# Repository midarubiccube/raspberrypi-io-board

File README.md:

# raspberrypi-io-board
## 基板画像

# 概要
- USB PD or 12V DC jack(40Vまで許容)
- 12v-5v, 12v-3.3v, 5v-1.2v DCDCコンバータ搭載
- USB3.0*2
- USB2.0*2
- M.2 M key (NVME SSDのみ) 
- M.2 E key
- gigabit ethernet
- hd*iっぽいなにかの端子
- SDカードスロット
- stm32H723VGT6 搭載
- CANFD*2
- stm32 debug用コネクタ

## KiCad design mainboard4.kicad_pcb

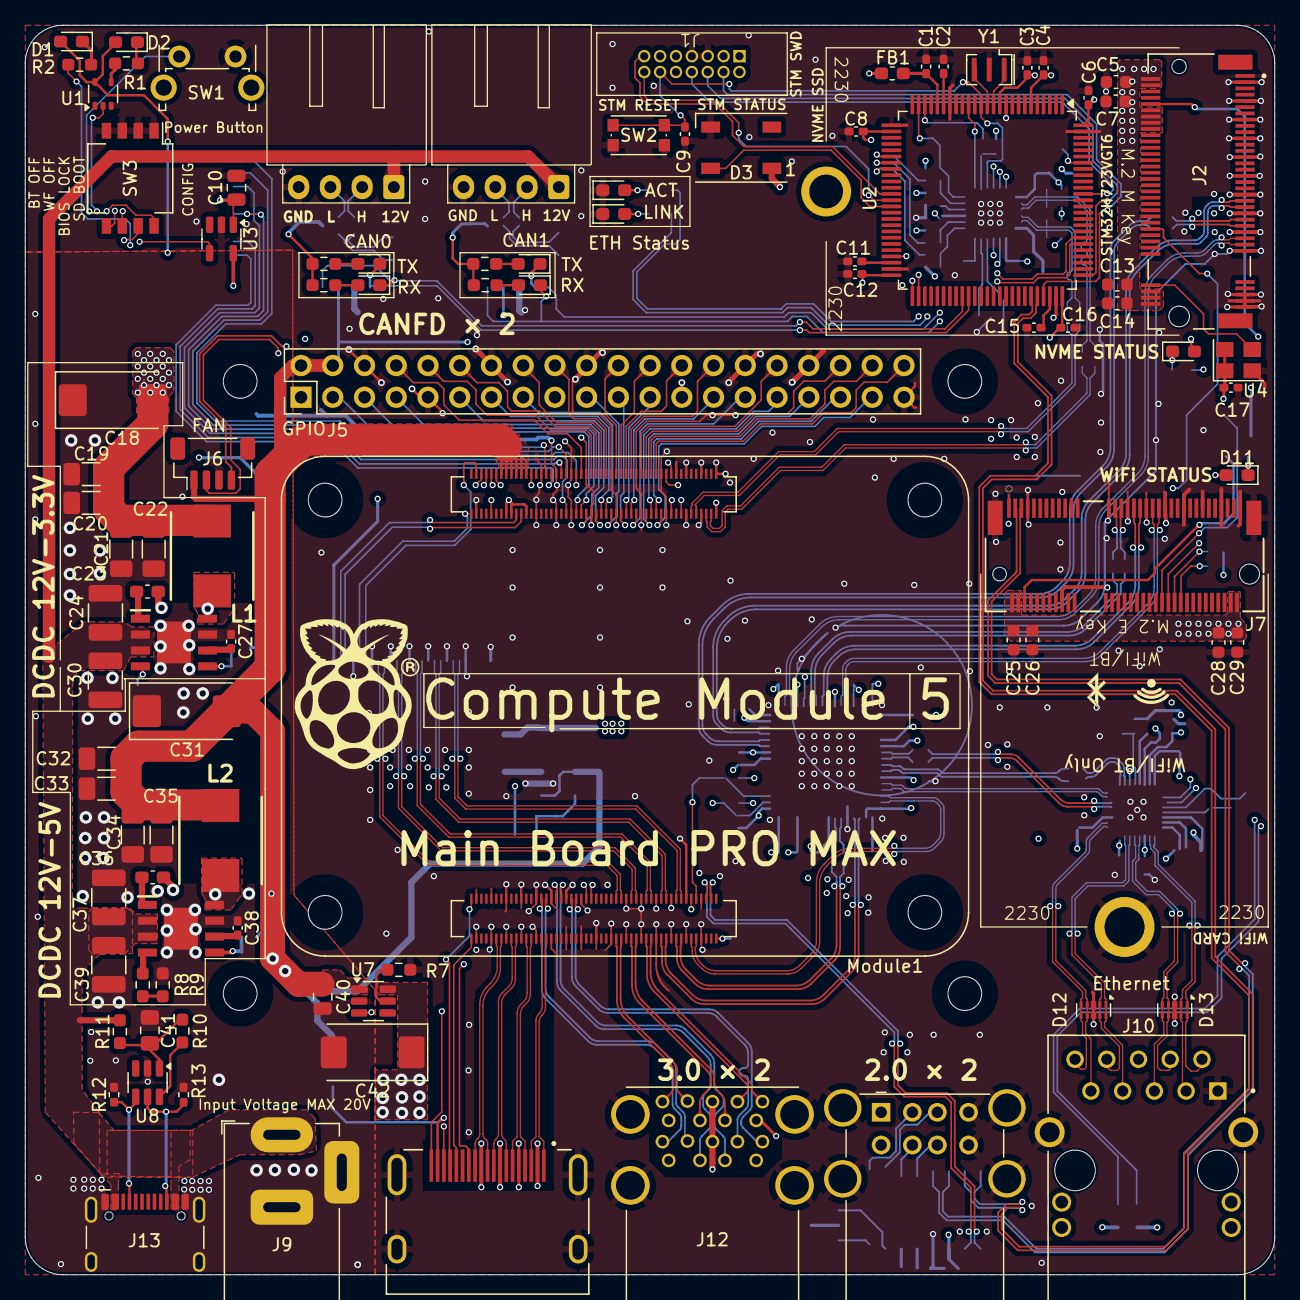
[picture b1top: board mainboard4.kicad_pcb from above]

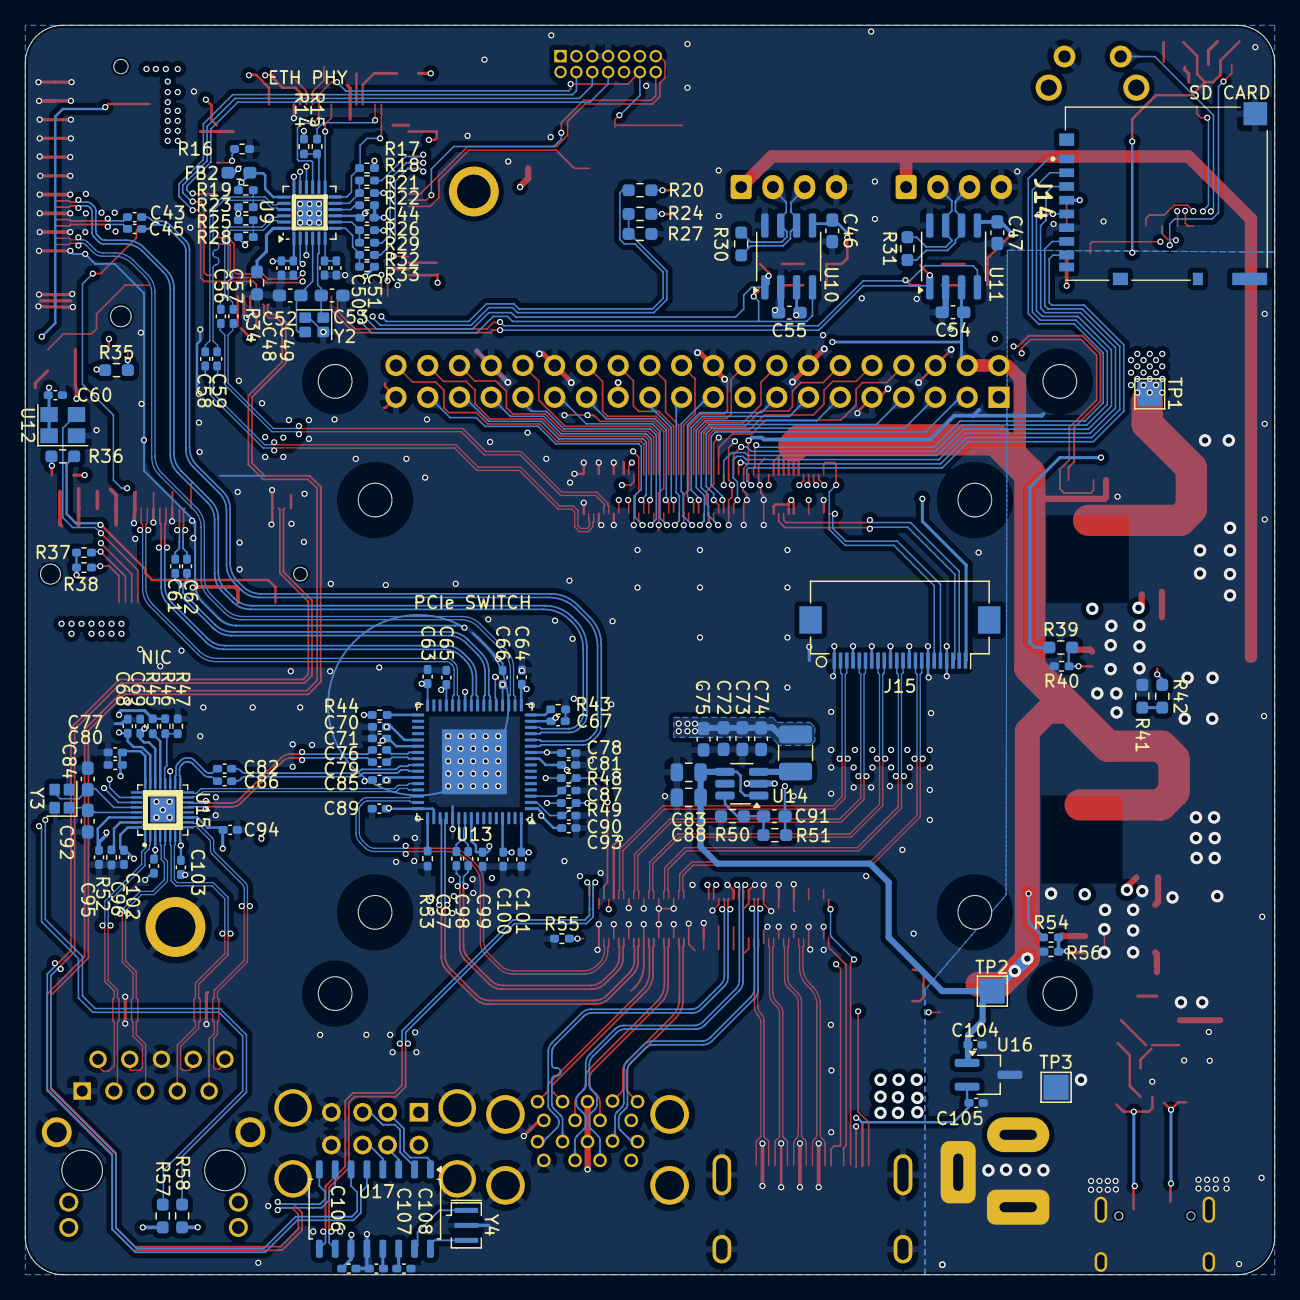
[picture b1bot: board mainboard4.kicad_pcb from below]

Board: 4 copper layers, 100.0 x 100.0 mm, 229 parts (130 on the bottom side), 251 nets.

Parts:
C1, C2, C3, C4, C6, C8, C12, C16, C43, C45, C61, C62, C63, C64, C65, C66, C67, C68, C69, C70, C71, C76, C77, C78, C79, C80, C81, C82, C85, C86, C89, C90, C93, C94, C95, C96, C97, C98, C99, C100, C101, C102, C103: 0.1uF; C_0402_1005Metric_Pad0.74x0.62mm_HandSolder
C5, C7, C13, C25, C26, C29: 0.1uF; C_0603_1608Metric
C9, C11, C15, C44, C48, C49, C56, C57, C58, C59: 0.1μF; C_0402_1005Metric_Pad0.74x0.62mm_HandSolder
C10, C40, C83, C88: 10u; C_0805_2012Metric
C14, C28: 0.01uF; C_0603_1608Metric
C17, C60, C104, C105: 100n; C_0402_1005Metric_Pad0.74x0.62mm_HandSolder
C18, C31: 100uF; CP_EIA-7343-30_AVX-N_Pad2.25x2.55mm_HandSolder
C19, C20, C21, C22, C32, C33, C34, C35: 22uF; C_1206_3216Metric_Pad1.33x1.80mm_HandSolder
C23, C36, C46, C47, C54, C55: 0.1uF; C_0603_1608Metric_Pad1.08x0.95mm_HandSolder
C24, C30, C37, C39: 10μF; C_1210_3225Metric_Pad1.33x2.70mm_HandSolder
C27, C38: 0.01uF; C_0402_1005Metric_Pad0.74x0.62mm_HandSolder
C41: 1μF; C_0805_2012Metric_Pad1.18x1.45mm_HandSolder
C42: 100uF; CP_EIA-7343-31_Kemet-D
C50: 1μF; C_0402_1005Metric_Pad0.74x0.62mm_HandSolder
C51: 470p; C_0402_1005Metric_Pad0.74x0.62mm_HandSolder
C52, C53, C84, C92: 15pF; C_0603_1608Metric_Pad1.08x0.95mm_HandSolder
C72, C73, C74, C75: 10u; C_0603_1608Metric_Pad1.08x0.95mm_HandSolder
C87: 1uF; C_0402_1005Metric_Pad0.74x0.62mm_HandSolder
C91: 22pF; C_0603_1608Metric_Pad1.08x0.95mm_HandSolder
C106, C107, C108: 0.1u; C_0402_1005Metric_Pad0.74x0.62mm_HandSolder
D1, D10, D11: LED Green; LED_0603_1608Metric_Pad1.05x0.95mm_HandSolder
D2: LED Red; LED_0603_1608Metric_Pad1.05x0.95mm_HandSolder
D3: WS2812B; LED_WS2812B_PLCC4_5.0x5.0mm_P3.2mm
D4, D5, D6, D7, D8, D9: LED; LED_0603_1608Metric_Pad1.05x0.95mm_HandSolder
D12, D13: H5VU25U; Diodes_UDFN-10_1.0x2.5mm_P0.5mm
FB1, FB2: FerriteBead; L_0603_1608Metric_Pad1.05x0.95mm_HandSolder
H1, H2: MountingHole; MountingHole_2.7mm_M2.5_DIN965
J1: Conn_02x07_Odd_Even; connector
J2: Bus_M.2_Socket_M; M.2 M Key socket
J3, J4: Conn_01x04_Pin; pocketheader4
J5: THD-20-R; PinHeader_2x20_P2.54mm_Vertical
J6: JST_SHBM04B-SRSS-TB; JST_SH_BM04B-SRSS-TB_1x04-1MP_P1.00mm_Vertical
J7: Bus_M.2_Socket_E; M.2 E Key socket
J8: USB_A_Stacked; USB_A_Wuerth_61400826021_Horizontal_Stacked
J9: Barrel_Jack; BarrelJack_Horizontal
J10: RJMG201K21120FR; AMPHENOL_RJMG201K21120FR
J11: 690-019-298-412; EDAC 690-019-298-412
J12: USB3_A; MTCONN_UBAF30-D2011
J13: USB_C_Receptacle_USB2.0_16P; USB_C_Receptacle_HCTL_HC-TYPE-C-16P-01A
J14: Micro_SD_Card_Det; DM3ATSFPEJM542
J15: Conn_01x22_Female; Hirose_FH12-22S-0.5SH_1x22-1MP_P0.50mm_Horizontal
L1: 6.8; INDPM7066X300N
L2: 6.8uH; INDPM7066X300N
L3: 2.2uH; L_1210_3225Metric_Pad1.42x2.65mm_HandSolder
Module1: Compute Module 5; Raspberry-Pi-5-Compute-Module
R1, R2, R3, R4, R5, R6, R35, R36: 1k; R_0603_1608Metric_Pad0.98x0.95mm_HandSolder
R7: 15K 1%; R_0603_1608Metric_Pad0.98x0.95mm_HandSolder
R8, R9, R41, R42, R50, R51: 100kΩ; R_0603_1608Metric_Pad0.98x0.95mm_HandSolder
R10: 47kΩ; R_0603_1608Metric_Pad0.98x0.95mm_HandSolder
R11: 1kΩ; R_0603_1608Metric_Pad0.98x0.95mm_HandSolder
R12, R13: 5.1kΩ; R_0402_1005Metric_Pad0.72x0.64mm_HandSolder
R14, R21, R26, R33: 10KΩ; R_0402_1005Metric_Pad0.72x0.64mm_HandSolder
R15, R18, R29, R32: 33Ω; R_0402_1005Metric_Pad0.72x0.64mm_HandSolder
R16, R22, R40, R55, R56: 10kΩ; R_0402_1005Metric_Pad0.72x0.64mm_HandSolder
R17: 1.5KΩ; R_0402_1005Metric_Pad0.72x0.64mm_HandSolder
R19, R23, R25, R28: 49.9Ω; R_0402_1005Metric_Pad0.72x0.64mm_HandSolder
R20, R24: 200; R_0603_1608Metric_Pad0.98x0.95mm_HandSolder
R27: 10k; R_0603_1608Metric_Pad0.98x0.95mm_HandSolder
R30, R31: 120Ω; R_0603_1608Metric_Pad0.98x0.95mm_HandSolder
R34: 10kΩ; R_0603_1608Metric_Pad0.98x0.95mm_HandSolder
R37: 1k; R_0402_1005Metric_Pad0.72x0.64mm_HandSolder
R38: 100k; R_0402_1005Metric_Pad0.72x0.64mm_HandSolder
R39: 31.6kΩ; R_0603_1608Metric_Pad0.98x0.95mm_HandSolder
R43, R49, R53: 12.1K; R_0402_1005Metric_Pad0.72x0.64mm_HandSolder
R44, R48: 4.7K; R_0402_1005Metric_Pad0.72x0.64mm_HandSolder
R45, R46, R47: 4.7kΩ; R_0402_1005Metric_Pad0.72x0.64mm_HandSolder
R52: 2.49kΩ; R_0402_1005Metric_Pad0.72x0.64mm_HandSolder
R54: 51.2kΩ; R_0402_1005Metric_Pad0.72x0.64mm_HandSolder
R57, R58: 470R; R_0603_1608Metric_Pad0.98x0.95mm_HandSolder
SW1: Right angle Tact button; SW_Tactile_SPST_Angled_PTS645Vx58-2LFS
SW2: SW_Push; SW_Push_1P1T_NO_CK_KMR2
SW3: SW_DIP_x04; SW_DIP_SPSTx04_Slide_KingTek_DSHP04TS_W7.62mm_P1.27mm
TP1, TP2, TP3: TestPoint; TestPoint_Pad_2.0x2.0mm
U1: 74LVC1G07SE-7; SOT-353_SC-70-5
U2: STM32H723VGT6; LQFP-100_14x14mm_P0.5mm
U3: RT9742GGJ5; SOT-23-5
U4, U12: ASEK-32.768KHZ-L-R-T; Crystal_SMD_3225-4Pin_3.2x2.5mm
U5: AP64502QSP-13; SOIC127P600X163-9N
U6: AP64502; SOIC127P600X163-9N
U7: AP22653W6; SOT-23-6
U8: CH221K; SOT-23-6
U9: LAN8742A; VQFN-24-1EP_4x4mm_P0.5mm_EP2.5x2.5mm
U10, U11: MCP2562-E-SN; SOIC-8_3.9x4.9mm_P1.27mm
U13: QFN-64-1EP_9x9mm_P0.5mm_EP5.2x5.2mm
U14: AP3445LW6-7; SOT-23-6_Handsoldering
U15: RTL8111H-CG-RH; QFN40P400X400X90-33N
U16: RT9742SNGV; TSOT-23_HandSoldering
U17: SL2.1A; SOIC-16_4.55x10.3mm_P1.27mm
Y1: 16Mhz; Resonator_SMD_Murata_CSTxExxV-3Pin_3.0x1.1mm
Y2, Y3: 25Mhz; Crystal_SMD_SeikoEpson_FA128-4Pin_2.0x1.6mm
Y4: 12Mhz; Resonator_SMD_Murata_CSTxExxV-3Pin_3.0x1.1mm

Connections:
+1.2V: C64.2, C65.2, C66.2, C67.2, C70.2, C72.1, C73.1, C74.1, C75.1, C81.2, C85.2, C89.2, C91.1, C100.2, C101.2, L3.2, R51.1, U13.9 (VDD12), U13.15 (VDD12), U13.17 (VCC12), U13.20 (VDD12), U13.26 (VDD12), U13.29 (VCC12), U13.37 (VDD12), U13.43 (VDD12), U13.48 (VCC12), U13.50 (VDD12), U13.61 (VDD12), U13.64 (VCC12)
+3.3V: C3.1, C4.1, C5.1, C6.1, C7.1, C8.1, C12.1, C13.1, C14.1, C16.1, C17.1, C18.2, C19.2, C20.2, C21.2, C22.2, C25.1, C26.1, C28.1, C29.1, C44.1, C46.1, C47.1, C60.1, C63.2, C68.2, C71.2, C78.1, C93.2, C94.2, C96.2, C99.2, D1.2 (A), D2.2 (A), D3.1 (VDD), D10.2 (A), D11.2 (A), FB1.1, FB2.1, J1.3, J2.2 (3.3V), J2.4 (3.3V), J2.12 (3.3V), J2.14 (3.3V), J2.16 (3.3V), J2.18 (3.3V), J2.70 (3.3V), J2.72 (3.3V), J2.74 (3.3V), J7.2 (3.3V), J7.4 (3.3V), J7.72 (3.3V), J7.74 (3.3V), J10.L2, J10.L4, J15.22, L1.2, R3.1, R4.1, R5.1, R6.1, R14.1, R17.1, R21.1, R26.1, R33.1, R37.1, R38.1, R39.1, R44.1, R45.2, R46.2, R48.1, R49.1, TP1.1, U1.5 (VCC), U2.6 (VBAT), U2.11 (VDD), U2.27 (VDD), U2.50 (VDD), U2.75 (VDD), U2.100 (VDD), U3.5 (IN), U4.1 (EN), U4.4 (VDD), U9.9 (VDDIO), U10.5 (Vio), U11.5 (Vio), U12.1 (EN), U12.4 (VDD), U13.1 (VSUS33), U13.10 (VDDA33), U13.21 (VDDA33), U13.32 (VCC3), U13.38 (VDDA33), U13.56 (VDDA33), U15.11 (AVDD33), U15.23 (VDDREG), U15.32 (AVDD33)
+5V: C31.2, C32.2, C33.2, C34.2, C35.2, C40.1, C54.1, C55.1, C83.1, C88.1, C104.1, J5.2, J5.4, J6.1, L2.2, Module1.77 (+5v_(Input)), Module1.79 (+5v_(Input)), Module1.81 (+5v_(Input)), Module1.83 (+5v_(Input)), Module1.85 (+5v_(Input)), Module1.87 (+5v_(Input)), R54.1, TP2.1, U7.1 (IN), U10.3 (VDD), U11.3 (VDD), U14.1 (EN), U14.4 (VIN), U16.1 (IN)
+12V: C24.1, C30.1, C37.1, C39.1, J3.1, J4.1, J9.1, J13.A4 (VBUS), J13.A9 (VBUS), J13.B4 (VBUS), J13.B9 (VBUS), R11.1, U5.2 (VIN), U5.3 (EN), U6.2 (VIN), U6.3 (EN)
/CANFD1/CANN: J3.3, R31.1, U11.6 (CANL)
/CANFD1/CANP: J3.2, R31.2, U11.7 (CANH)
/CANFD1/CANRX: D8.1 (K), U2.59 (PD12), U11.4 (RXD)
/CANFD1/CANTX: D6.1 (K), U2.60 (PD13), U11.1 (TXD)
/CANFD2/CANN: J4.3, R30.1, U10.6 (CANL)
/CANFD2/CANP: J4.2, R30.2, U10.7 (CANH)
/CANFD2/CANRX: D9.1 (K), U2.81 (PD0), U10.4 (RXD)
/CANFD2/CANTX: D7.1 (K), U2.82 (PD1), U10.1 (TXD)
/CM5/3.3V: J5.1, J5.17, Module1.78 (GPIO_VREF(1.8v/3.3v_Input)), Module1.84 (+3.3v_(Output)), Module1.86 (+3.3v_(Output))
/CM5/BT_nDis: Module1.91 (BT_nDisable), SW3.5
/CM5/CEC: J11.13 (CEC), Module1.151 (HDMI0_CEC)
/CM5/CKN: J11.12 (CK-), Module1.190 (HDMI0_CLK_N)
/CM5/CKP: J11.10 (CK+), Module1.188 (HDMI0_CLK_P)
/CM5/D0N: J11.9 (D0-), Module1.184 (HDMI0_TX0_N)
/CM5/D0P: J11.7 (D0+), Module1.182 (HDMI0_TX0_P)
/CM5/D1N: J11.6 (D1-), Module1.178 (HDMI0_TX1_N)
/CM5/D1P: J11.4 (D1+), Module1.176 (HDMI0_TX1_P)
/CM5/D2N: J11.3 (D2-), Module1.172 (HDMI0_TX2_N)
/CM5/D2P: J11.1 (D2+), Module1.170 (HDMI0_TX2_P)
/CM5/DSI0N: J15.2, Module1.115 (MIPI0_D0_N)
/CM5/DSI0P: J15.3, Module1.117 (MIPI0_D0_P)
/CM5/DSI1N: J15.5, Module1.121 (MIPI0_D1_N)
/CM5/DSI1P: J15.6, Module1.123 (MIPI0_D1_P)
/CM5/DSI2N: J15.11, Module1.133 (MIPI0_D2_N)
/CM5/DSI2P: J15.12, Module1.135 (MIPI0_D2_P)
/CM5/DSI3N: J15.14, Module1.139 (MIPI0_D3_N)
/CM5/DSI3P: J15.15, Module1.141 (MIPI0_D3_P)
/CM5/DSICN: J15.8, Module1.127 (MIPI0_C_N)
/CM5/DSICP: J15.9, Module1.129 (MIPI0_C_P)
/CM5/EEPROM_nWP: Module1.20 (EEPROM_nWP), SW3.7
/CM5/GPIO0: J15.17, Module1.97 (CAM_GPIO0)
/CM5/GPIO1: J15.18, Module1.100 (CAM_GPIO1)
/CM5/GPIO2: J5.3, Module1.58 (GPIO2)
/CM5/GPIO3: J5.5, Module1.56 (GPIO3)
/CM5/GPIO4: J5.7, Module1.54 (GPIO4)
/CM5/GPIO5: J5.29, Module1.34 (GPIO5)
/CM5/GPIO6: J5.31, Module1.30 (GPIO6)
/CM5/GPIO7: J5.26, Module1.37 (GPIO7)
/CM5/GPIO8: J5.24, Module1.39 (GPIO8)
/CM5/GPIO9: J5.21, Module1.40 (GPIO9)
/CM5/GPIO10: J5.19, Module1.44 (GPIO10)
/CM5/GPIO11: J5.23, Module1.38 (GPIO11)
/CM5/GPIO12: J5.32, Module1.31 (GPIO12)
/CM5/GPIO13: J5.33, Module1.28 (GPIO13)
/CM5/GPIO14: J5.8, Module1.55 (GPIO14)
/CM5/GPIO15: J5.10, Module1.51 (GPIO15)
/CM5/GPIO16: J5.36, Module1.29 (GPIO16)
/CM5/GPIO17: J5.11, Module1.50 (GPIO17)
/CM5/GPIO18: J5.12, Module1.49 (GPIO18)
/CM5/GPIO19: J5.35, Module1.26 (GPIO19)
/CM5/GPIO20: J5.38, Module1.27 (GPIO20)
/CM5/GPIO21: J5.40, Module1.25 (GPIO21)
/CM5/GPIO22: J5.15, Module1.46 (GPIO22)
/CM5/GPIO23: J5.16, Module1.47 (GPIO23)
/CM5/GPIO24: J5.18, Module1.45 (GPIO24)
/CM5/GPIO25: J5.22, Module1.41 (GPIO25)
/CM5/GPIO26: J5.37, Module1.24 (GPIO26)
/CM5/GPIO27: J5.13, Module1.48 (GPIO27)
/CM5/HOST.CLKN: Module1.112 (PCIe_CLK_N), U13.46 (REFCLKP_0)
/CM5/HOST.CLKP: Module1.110 (PCIe_CLK_P), U13.47 (REFCLKN_0)
/CM5/HOST.CLKREQ: Module1.102 (PCIe_nCLKREQ), R55.2
/CM5/HOST.RXN: C97.1, Module1.118 (PCIe_RX_N)
/CM5/HOST.RXP: C98.1, Module1.116 (PCIe_RX_P)
/CM5/HOST.TXN: Module1.124 (PCIe_TX_N), U13.51 (RXP_0)
/CM5/HOST.TXP: Module1.122 (PCIe_TX_P), U13.52 (RXN_0)
/CM5/HPD: J11.19 (HPD/HEAC-), Module1.153 (HDMI0_HOTPLUG)
/CM5/ID_SC: J5.28, Module1.35 (ID_SC)
/CM5/ID_SD: J5.27, Module1.36 (ID_SD)
/CM5/LED_nACT: Module1.21 (LED_nACT), R2.2
/CM5/PCIe_nRST: C87.2, Module1.109 (PCIe_nRST), R48.2, U13.3 (PE_RST)
/CM5/POWER_SW: Module1.92 (PWR_BUT), SW1.1
/CM5/PWM: J6.2, Module1.19 (FAN_PWM)
/CM5/PWR_ON: Module1.75 (SD_PWR_ON), U3.4 (EN)
/CM5/SCL: J11.15 (SCL), Module1.200 (HDMI0_SCL)
/CM5/SDA: J11.16 (SDA), Module1.199 (HDMI0_SDA)
/CM5/SD_CLK: J14.5 (CLK), Module1.57 (SD_CLK)
/CM5/SD_CMD: J14.3 (CMD), Module1.62 (SD_CMD)
/CM5/SD_DAT0: J14.7 (DAT0), Module1.63 (SD_DAT0)
/CM5/SD_DAT1: J14.8 (DAT1), Module1.67 (SD_DAT1)
/CM5/SD_DAT2: J14.1 (DAT2), Module1.69 (SD_DAT2)
/CM5/SD_DAT3: J14.2 (DAT3/CD), Module1.61 (SD_DAT3)
/CM5/TACHO: J6.4, Module1.16 (FAN_TACHO)
/CM5/TP_SCL: J15.20, Module1.80 (SCL0)
/CM5/TP_SDA: J15.21, Module1.82 (SDA0)
/CM5/TRD0_N: C56.1, Module1.10 (Ethernet_Pair0_N)
/CM5/TRD0_P: C57.1, Module1.12 (Ethernet_Pair0_P)
/CM5/TRD1_N: C58.1, Module1.6 (Ethernet_Pair1_N)
/CM5/TRD1_P: C59.1, Module1.4 (Ethernet_Pair1_P)
/CM5/USB0.DN: J12.B2 (D-), Module1.136 (USB3-0-D_N)
/CM5/USB0.DP: J12.B3 (D+), Module1.134 (USB3-0-D_P)
/CM5/USB0.RXN: J12.B5 (SSRX-), Module1.128 (USB3-0-RX_N)
/CM5/USB0.RXP: J12.B6 (SSRX+), Module1.130 (USB3-0-RX_P)
/CM5/USB0.TXN: J12.B8 (SSTX-), Module1.140 (USB3-0-TX_N)
/CM5/USB0.TXP: J12.B9 (SSTX+), Module1.142 (USB3-0-TX_P)
/CM5/USB1.DN: J12.A2 (D-), Module1.165 (USB3-1-D_N)
/CM5/USB1.DP: J12.A3 (D+), Module1.163 (USB3-1-D_P)
/CM5/USB1.RXN: J12.A5 (SSRX-), Module1.157 (USB3-1-RX_N)
/CM5/USB1.RXP: J12.A6 (SSRX+), Module1.159 (USB3-1-RX_P)
/CM5/USB1.TXN: J12.A8 (SSTX-), Module1.169 (USB3-1-TX_N)
/CM5/USB1.TXP: J12.A9 (SSTX+), Module1.171 (USB3-1-TX_P)
/CM5/USB2.DN: Module1.103 (USB2_N), U17.9 (UDM)
/CM5/USB2.DP: Module1.105 (USB2_P), U17.10 (UDP)
/CM5/VBUS_EN: Module1.111 (VBUS_EN), U7.3 (EN)
/CM5/WL_nDis: Module1.89 (WiFi_nDisable), SW3.6
/CM5/nPWR_LED: Module1.95 (LED_nPWR), U1.2
/CM5/nRPIBOOT: Module1.93 (nRPIBOOT), SW3.8
/CM5_INTERFACE/GPDI_5v: C105.1, J11.18 (+5V), U16.2 (OUT)
/Ethernet PHY/CRSDV: R18.2, U2.31 (PA7)
/Ethernet PHY/MDC: U2.16 (PC1), U9.13 (MDC)
/Ethernet PHY/MDIO: R17.2, U2.24 (PA2), U9.12 (MDIO)
/Ethernet PHY/REFCLK: R15.1, U2.23 (PA1)
/Ethernet PHY/RXC_N: C56.2, R25.2, U9.22 (RXN)
/Ethernet PHY/RXC_P: C57.2, R28.2, U9.23 (RXP)
/Ethernet PHY/RXD0: R29.2, U2.32 (PC4)
/Ethernet PHY/RXD1: R32.2, U2.33 (PC5)
/Ethernet PHY/TXC_N: C58.2, R19.2, U9.20 (TXN)
/Ethernet PHY/TXC_P: C59.2, R23.2, U9.21 (TXP)
/Ethernet PHY/TXD0: U2.51 (PB12), U9.17 (TXD0)
/Ethernet PHY/TXD1: U2.52 (PB13), U9.18 (TXD1)
/Ethernet PHY/TXEN: U2.47 (PB11), U9.16 (TXEN)
/MCU/LED: D3.4 (DIN), U2.39 (PE9)
/MCU/MCU.DN: U2.70 (PA11), U17.7 (DM1)
/MCU/MCU.DP: U2.71 (PA12), U17.8 (DP1)
/MCU/SWCLK: J1.6, U2.76 (PA14(JTCK)
/MCU/SWDIO: J1.4, U2.72 (PA13(JTMS)
/MCU/SWO: J1.8, U2.89 (PB3(JTDO)
/MCU/UART_RX: J1.13, U2.37 (PE7)
/MCU/UART_TX: J1.14, U2.38 (PE8)
/MCU/VDDA: C1.1, FB1.2, U2.21 (VDDA)
/MCU/~RST: C9.1, J1.12, SW2.2, U2.14 (NRST), U9.15 (~RST)
/NIC/1.0V: C69.2, C77.2, C80.2, C95.2, C102.2, C103.2, U15.3 (AVDD10), U15.8 (AVDD10), U15.22 (DVDD10), U15.24 (REGOUT), U15.30 (AVDD10)
/NIC/ETH_LEDG: R57.2, U15.27 (LED0)
/NIC/ETH_LEDY: R58.2, U15.26 (LED1)
/NIC/HSON: C86.2, U15.17 (HSOP)
/NIC/HSOP: C82.2, U15.18 (HSON)
/NIC/MDI0+: D13.1, D13.10 (NC), J10.P2 (TD1+), U15.1 (MDIP0)
/NIC/MDI0-: D13.2, D13.9 (NC), J10.P3 (TD1-), U15.2 (MDIN0)
/NIC/MDI1+: D13.4, D13.7 (NC), J10.P4 (TD2+), U15.4 (MDIP1)
/NIC/MDI1-: D13.5, D13.6 (NC), J10.P5 (TD2-), U15.5 (MDIN1)
/NIC/MDI2+: D12.1, D12.10 (NC), J10.P7 (TD3+), U15.6 (MDIP2)
/NIC/MDI2-: D12.2, D12.9 (NC), J10.P8 (TD3-), U15.7 (MDIN2)
/NIC/MDI3+: D12.4, D12.7 (NC), J10.P9 (TD4+), U15.9 (MDIP3)
/NIC/MDI3-: D12.5, D12.6 (NC), J10.P10 (TD4-), U15.10 (MDIN3)
/NIC/NIC.CLKN: U13.45 (REFCLKN_7), U15.15 (REFCLK_P)
/NIC/NIC.CLKP: U13.44 (REFCLKP_7), U15.16 (REFCLK_N)
/NIC/NIC.RXN: C86.1, U13.42 (RXN_7)
/NIC/NIC.RXP: C82.1, U13.41 (RXP_7)
/NIC/NIC.TXN: C79.1, U15.13 (HSIP)
/NIC/NIC.TXP: C76.1, U15.14 (HSIN)
/NIC/nRST: C90.2, J2.50 (~PERST), J7.52 (~PERST0), R49.2, U13.2 (PE_RST_OUT), U15.19 (PERSTB)
/NVME/NVME.CLKN: J2.55 (REFCLKp), U13.19 (REFCLKN_3)
/NVME/NVME.CLKP: J2.53 (REFCLKn), U13.18 (REFCLKP_3)
/NVME/NVME.RXN: J2.43 (PERp0/SATA-B-), U13.14 (RXN_3)
/NVME/NVME.RXP: J2.41 (PERn0/SATA-B+), U13.13 (RXP_3)
/NVME/NVME.TXN: C43.1, J2.47 (PETn0/SATA-A-)
/NVME/NVME.TXP: C45.1, J2.49 (PETp0/SATA-A+)
/PCIe_SW/HOST.RXCN: C98.2, U13.55 (TXN_0)
/PCIe_SW/HOST.RXCP: C97.2, U13.54 (TXP_0)
/PCIe_SW/NIC.TXCN: C79.2, U13.40 (TXN_7)
/PCIe_SW/NIC.TXCP: C76.2, U13.39 (TXP_3)
/PCIe_SW/NVME.TXCN: C45.2, U13.12 (TXN_3)
/PCIe_SW/NVME.TXCP: C43.2, U13.11 (TXP_3)
/PCIe_SW/WiFi.CLKN: J7.49 (REFCLKn0), U13.28 (REFCLKN_5)
/PCIe_SW/WiFi.CLKP: J7.47 (REFCLKp0), U13.27 (REFCLKP_5)
/PCIe_SW/WiFi.RXN: J7.43 (PERn0), U13.25 (RXN_5)
/PCIe_SW/WiFi.RXP: J7.41 (PERp0), U13.24 (RXP_5)
/PCIe_SW/WiFi.TXCN: C61.2, U13.23 (TXN_5)
/PCIe_SW/WiFi.TXCP: C62.2, U13.22 (TXP_5)
/PCIe_SW/WiFi.TXN: C61.1, J7.37 (PETn0)
/PCIe_SW/WiFi.TXP: C62.1, J7.35 (PETp0)
/Power/CC1: J13.A5 (CC1), R12.1, U8.4 (CC1)
/Power/CC2: J13.B5 (CC2), R13.1, U8.5 (CC2)
/USB/D3N: J8.6 (D2-), U17.3 (DM3)
/USB/D3P: J8.7 (D2+), U17.4 (DP3)
/USB/D4N: J8.2 (D1-), U17.1 (DM4)
/USB/D4P: J8.3 (D1+), U17.2 (DP4)
/USB/WiFi.DN: J7.5 (USB_D-), U17.5 (DM2)
/USB/WiFi.DP: J7.3 (USB_D+), U17.6 (DP2)
GND: C1.2, C2.2, C3.2, C4.2, C5.2, C6.2, C7.2, C8.2, C9.2, C10.2, C11.2, C12.2, C13.2, C14.2, C15.2, C16.2, C17.2, C18.1, C19.1, C20.1, C21.1, C22.1, C24.2, C25.2, C26.2, C27.1, C28.2, C29.2, C30.2, C31.1, C32.1, C33.1, C34.1, C35.1, C37.2, C38.1, C39.2, C40.2, C41.2, C42.2, C44.2, C46.2, C47.2, C48.2, C49.2, C50.2, C51.2, C52.2, C53.2, C54.2, C55.2, C60.2, C63.1, C64.1, C65.1, C66.1, C67.1, C68.1, C69.1, C70.1, C71.1, C72.2, C73.2, C74.2, C75.2, C77.1, C78.2, C80.1, C81.1, C83.2, C84.2, C85.1, C87.1, C88.2, C89.1, C90.1, C92.2, C93.1, C94.1, C95.1, C96.1, C99.1, C100.1, C101.1, C102.1, C103.1, C104.2, C105.2, C106.2, C107.2, C108.2, D3.3 (VSS), D4.1 (K), D5.1 (K), D12.3 (VSS), D12.8 (VSS), D13.3 (VSS), D13.8 (VSS), J1.5, J1.7, J2.1 (GND), J2.3 (GND), J2.9 (GND), J2.15 (GND), J2.21 (GND), J2.27 (GND), J2.33 (GND), J2.39 (GND), J2.45 (GND), J2.51 (GND), J2.57 (GND), J2.71 (GND), J2.73 (GND), J2.75 (GND), J3.4, J4.4, J5.6, J5.9, J5.14, J5.20, J5.25, J5.30, J5.34, J5.39, J6.3, J7.1 (GND), J7.7 (GND), J7.18 (GND), J7.33 (GND), J7.39 (GND), J7.45 (GND), J7.51 (GND), J7.57 (GND), J7.63 (GND), J7.69 (GND), J7.75 (GND), J7.76 (GND), J7.77 (GND), J7.M1 (GND), J8.4 (GND1), J8.8 (GND2), J8.9 (Shield), J9.2, J9.3, J10.P1 (GND), J10.P6 (TCT), J10.S1 (SHIELD), J10.S2 (SHIELD__1), J11.2 (D2S), J11.5 (D1S), J11.8 (D0S), J11.11 (CKS), J11.17 (GND), J11.SH1 (SH), J11.SH2 (SH), J11.SH3 (SH), J11.SH4 (SH), J12.10 (SHIELD), J12.A4 (GND), J12.A7 (DRAIN), J12.B4 (GND), J12.B7 (DRAIN), J13.A1 (GND), J13.A12 (GND), J13.B1 (GND), J13.B12 (GND), J13.S1 (SHIELD), J14.6 (VSS), J14.11 (SHIELD), J15.1, J15.4, J15.7, J15.10, J15.13, J15.16, J15.19, Module1.1 (GND), Module1.2 (GND), Module1.7 (GND), Module1.8 (GND), Module1.13 (GND), Module1.14 (GND), Module1.17 (Ethernet_nLED2(3.3v)), Module1.22 (GND), Module1.23 (GND), Module1.32 (GND), Module1.33 (GND), Module1.42 (GND), Module1.43 (GND), Module1.52 (GND), Module1.53 (GND), Module1.59 (GND), Module1.60 (GND), Module1.65 (GND), Module1.66 (GND), Module1.71 (GND), Module1.74 (GND), Module1.98 (GND), Module1.107 (GND), Module1.108 (GND), Module1.113 (GND), Module1.114 (GND), Module1.119 (GND), Module1.120 (GND), Module1.125 (GND), Module1.126 (GND), Module1.131 (GND), Module1.132 (GND), Module1.137 (GND), Module1.138 (GND), Module1.144 (GND), Module1.150 (GND), Module1.155 (GND), Module1.156 (GND), Module1.161 (GND), Module1.162 (GND), Module1.167 (GND), Module1.168 (GND), Module1.173 (GND), Module1.174 (GND), Module1.179 (GND), Module1.180 (GND), Module1.185 (GND), Module1.186 (GND), Module1.191 (GND), Module1.192 (GND), Module1.197 (GND), Module1.198 (GND), R7.2, R9.2, R12.2, R13.2, R16.1, R22.2, R27.2, R34.2, R40.2, R41.2, R43.2, R47.1, R50.2, R52.1, R53.2, R55.1, R56.2, SW1.2, SW2.1, SW3.1, SW3.2, SW3.3, SW3.4, TP3.1, U1.3 (GND), U2.10 (VSS), U2.19 (VSSA), U2.26 (VSS), U2.49 (VSS), U2.74 (VSS), U2.99 (VSS), U3.2 (GND), U4.2 (GND), U5.7 (GND), U6.7 (GND), U7.2 (GND), U8.2 (GND), U9.25 (VSS), U10.2 (VSS), U10.8 (STBY), U11.2 (VSS), U11.8 (STBY), U12.2 (GND), U13.53 (GNDA), U13.65 (GND), U14.2 (GND), U15.33 (GND), U16.3 (GND), U17.12 (GND), Y1.2, Y2.2, Y2.4, Y3.2, Y3.4, Y4.2
unnamed: C11.1, U2.48 (VCAP)
unnamed: C15.1, U2.73 (VCAP)
unnamed: D1.1 (K), R2.1
unnamed: D2.1 (K), R1.1
unnamed: D4.2 (A), R20.2
unnamed: D5.2 (A), R24.2
unnamed: D6.2 (A), R3.2
unnamed: D7.2 (A), R4.2
unnamed: D8.2 (A), R5.2
unnamed: D9.2 (A), R6.2
unnamed: D10.1 (K), R35.1
unnamed: D11.1 (K), R36.1
unnamed: J2.10 (DAS/~DSS/~LED1), R35.2
unnamed: J2.68 (SUSCLK), U4.3 (Out)
unnamed: J7.50 (SUSCLK), U12.3 (Out)
unnamed: J7.6 (~LED_1), R36.2
unnamed: J7.56 (~W_DISABLE1), R38.2
unnamed: J7.54 (~W_DISABLE2), R37.2
unnamed: J10.L1, R58.1
unnamed: J10.L3, R57.1
unnamed: R1.2, U1.4
unnamed: R8.2, R9.1
unnamed: R41.1, R42.2
unnamed: R16.2, U2.94 (BOOT0)
unnamed: U2.12 (PH0), Y1.1
unnamed: U2.13 (PH1), Y1.3
unnamed: C2.1, U2.20 (VREF+)
unnamed: C23.1, U5.1 (BST)
unnamed: R39.2, R40.1, U5.5 (FB)
unnamed: R42.1, U5.4 (RT/CLK)
unnamed: C27.2, U5.6 (SS)
unnamed: C23.2, L1.1, U5.8 (SW)
unnamed: C36.1, U6.1 (BST)
unnamed: R54.2, R56.1, U6.5 (FB)
unnamed: R8.1, U6.4 (RT/CLK)
unnamed: C38.2, U6.6 (SS)
unnamed: C36.2, L2.1, U6.8 (SW)
unnamed: R7.1, U7.5 (ILIM)
unnamed: R10.2, U8.6 (CFG)
unnamed: C41.1, R10.1, R11.2, U8.1 (VDD)
unnamed: R18.1, R21.2, U9.11 (CRS_DV/MODE2)
unnamed: R20.1, U9.3 (LED1/REGOFF)
unnamed: R24.1, R27.1, U9.2 (LED2/~INTSEL)
unnamed: R34.1, U9.24 (RBIAS)
unnamed: R26.2, R29.1, U9.8 (RXD0/MODE0)
unnamed: R32.1, R33.2, U9.7 (RXD1/MODE1)
unnamed: R22.1, U9.10 (RXER/PHYAD0)
unnamed: C48.1, C49.1, FB2.2, R19.1, R23.1, R25.1, R28.1, U9.1 (VDD2A), U9.19 (VDD1A)
unnamed: C50.1, C51.1, U9.6 (VDDCR)
unnamed: C53.1, U9.5 (XTAL1/CLKIN), Y2.1
unnamed: C52.1, U9.4 (XTAL2), Y2.3
unnamed: R14.2, R15.2, U9.14 (~INT/REFCLKO)
unnamed: R43.1, U13.16 (REXT1)
unnamed: R53.1, U13.49 (REXT2)
unnamed: R44.2, U13.33 (TEST_EN)
unnamed: C91.2, R50.1, R51.2, U14.6 (FB)
unnamed: L3.1, U14.3 (LX)
unnamed: C84.1, U15.28 (CKXTAL1), Y3.3
unnamed: C92.1, U15.29 (CKXTAL2), Y3.1
unnamed: R46.1, R47.2, U15.20 (ISOLATEB)
unnamed: R45.1, U15.21 (LANWAKEB)
unnamed: R52.2, U15.31 (RSET)
unnamed: C107.1, U17.13 (VDD3)
unnamed: C108.1, U17.14 (VDD18)
unnamed: U17.16 (XIN), Y4.3
unnamed: U17.15 (XOUT), Y4.1
SD_PWR: C10.1, J14.4 (VDD), U3.1 (OUT)
VBUS: C42.1, C106.1, J8.1 (VBUS1), J8.5 (VBUS2), J12.A1 (VBUS), J12.B1 (VBUS), U7.6 (OUT), U17.11 (VCC5V)

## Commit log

2025-06-02 init commit
2025-06-09 change cad data
2025-06-09 add image
2025-06-09 add README.md
2025-06-09 add pdf
2025-06-09 add readme PDF
2025-06-23 change clearance
2025-06-24 add mark
2025-06-24 change design
2025-06-24 change efuse
2025-06-26 change USB3.0 HUB design
2025-06-30 remove efuse
2025-07-02 add VBUS Line
2025-07-03 add capacitor
2025-07-03 change sata sch
2025-07-06 add sata capacitor
2025-07-13 add logo
2025-07-14 remove registor
2025-07-15 add logp
2025-07-15 change ethernet
2025-07-21 chenge postion usb2sata
2025-07-21 remove usb
2025-07-22 add pcie root
2025-07-22 change ethernet root
2025-07-24 add usb3.0
2025-07-24 change USB2.0
2025-07-25 add usb2.0 line
2025-07-27 add usb
2025-07-28 add pcie line
2025-08-04 add HDD_LED[
2025-08-04 end route
2025-08-04 fix usbline
2025-08-04 fix screen
2025-08-05 リセットラインのルートを変更
2025-08-08 add disable pin pullup
2025-08-28 Create LICENSE
2026-06-24 データをアップロード
2026-06-24 画像を差し替え
